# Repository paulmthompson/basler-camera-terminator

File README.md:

# basler-camera-terminator

This is the small circuit board to be used with basler IO cables to connect to BNC

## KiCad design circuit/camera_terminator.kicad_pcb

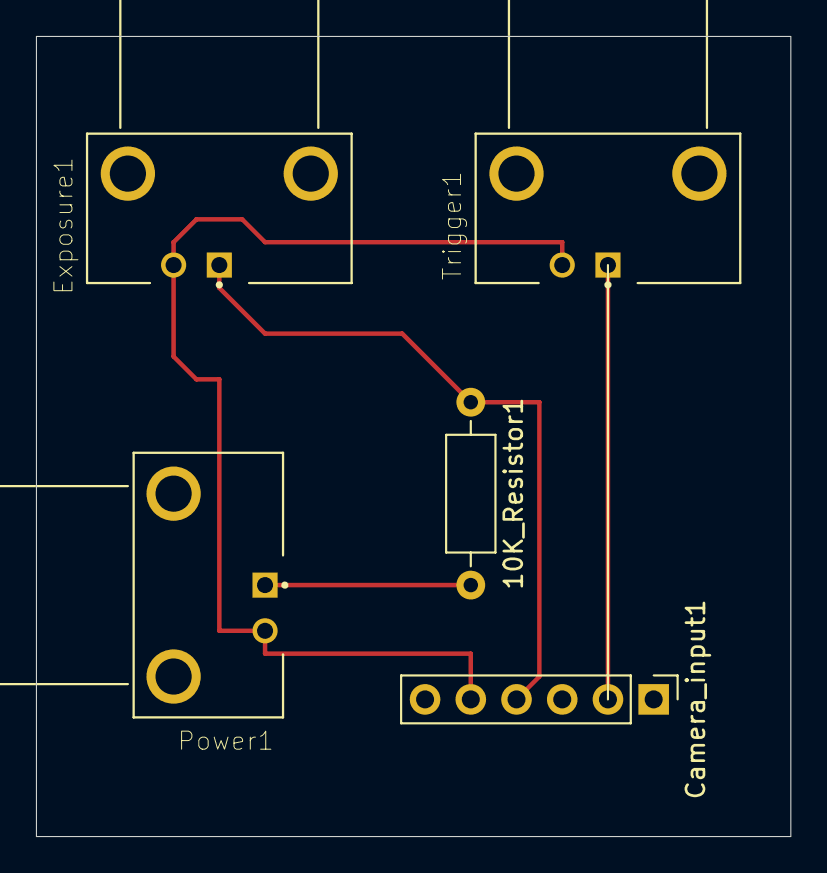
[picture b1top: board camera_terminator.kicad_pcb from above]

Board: 2 copper layers, 41.9 x 44.5 mm, 5 parts (0 on the bottom side), 4 nets.

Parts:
10K_Resistor1: 10k; R_Axial_DIN0207_L6.3mm_D2.5mm_P10.16mm_Horizontal
Camera_input1: Conn_01x06_Male; PinHeader_1x06_P2.54mm_Vertical
Exposure1: 1-1634612-0; TE_1-1634612-0
Power1: 1-1634612-0; TE_1-1634612-0
Trigger1: 1-1634612-0; TE_1-1634612-0

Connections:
GNDREF: Camera_input1.5, Exposure1.2, Power1.2, Trigger1.2
unnamed: 10K_Resistor1.1, Camera_input1.4, Exposure1.1
unnamed: 10K_Resistor1.2, Power1.1
unnamed: Camera_input1.2, Trigger1.1

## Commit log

2023-03-28 add circuit board files
